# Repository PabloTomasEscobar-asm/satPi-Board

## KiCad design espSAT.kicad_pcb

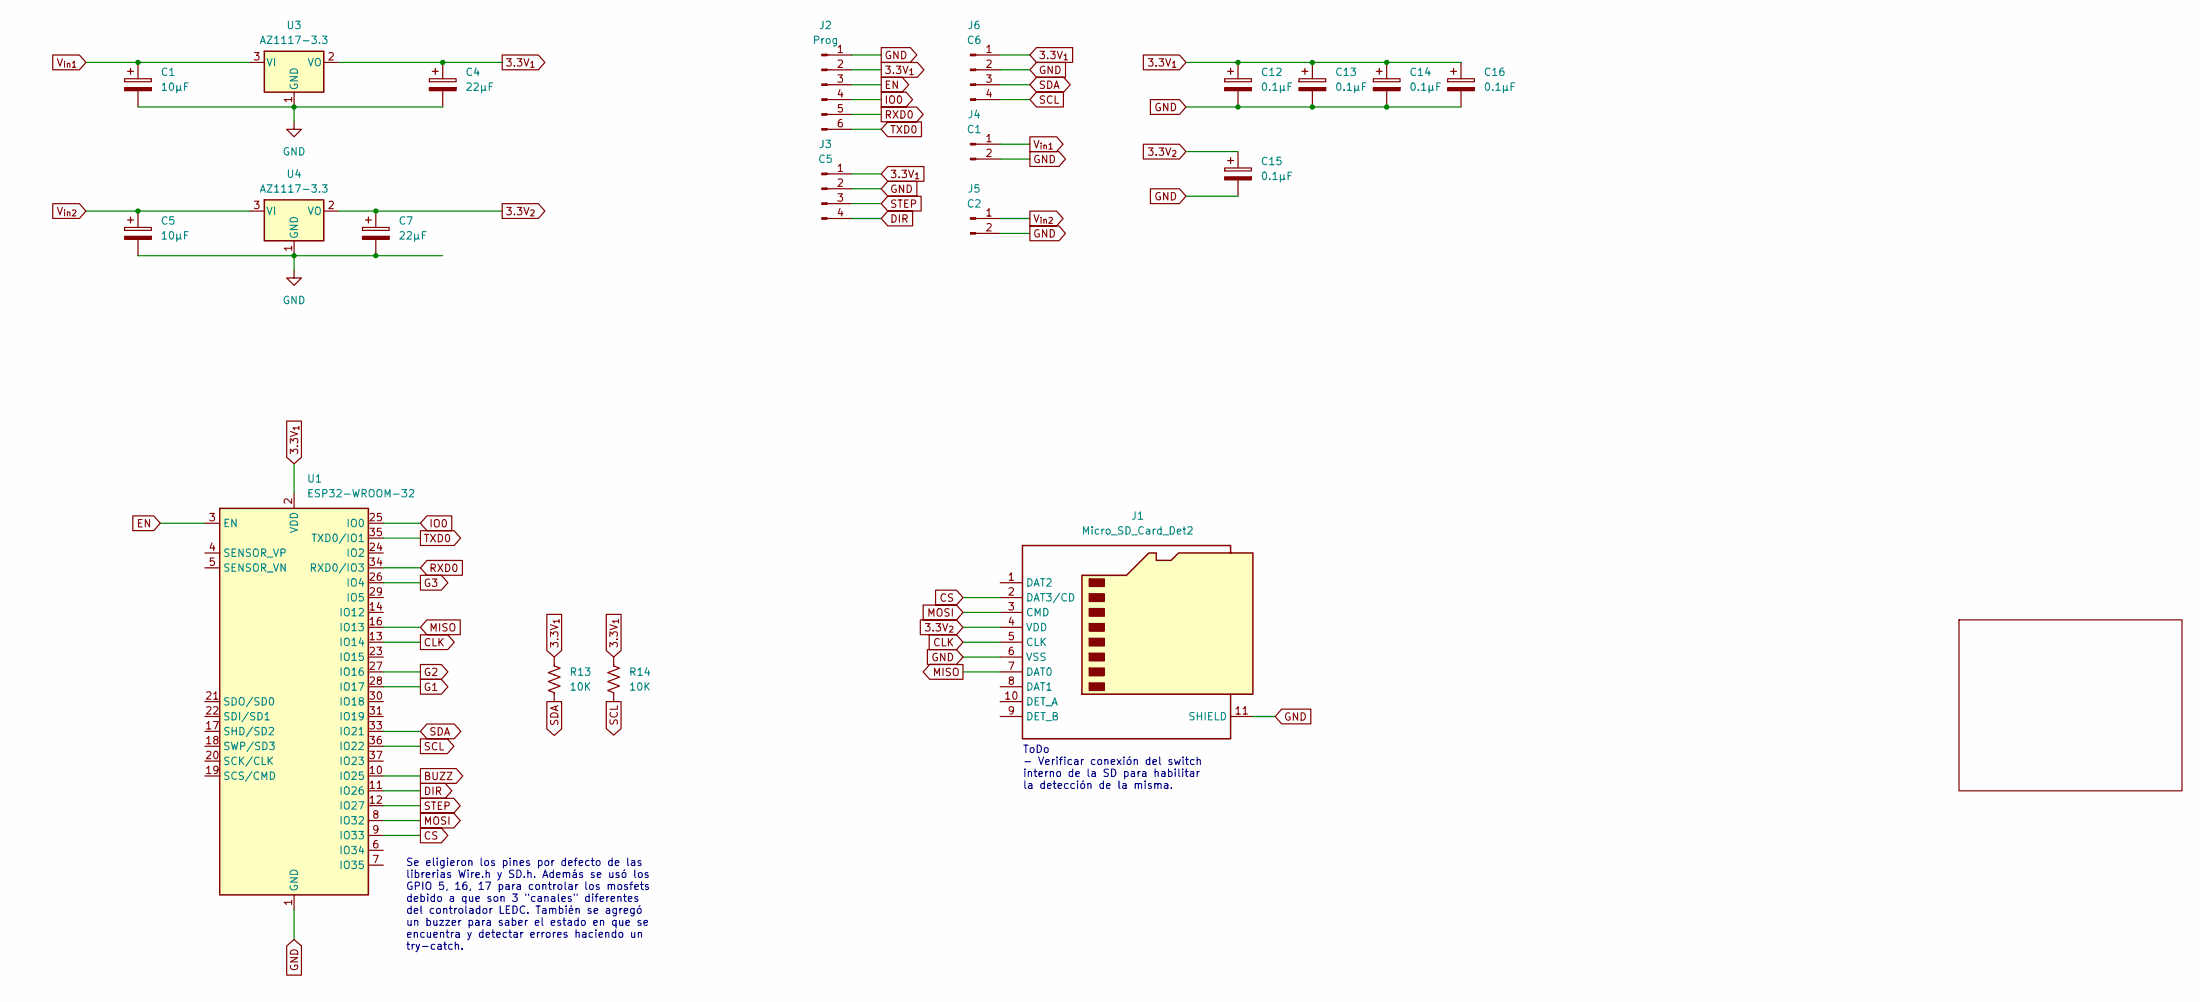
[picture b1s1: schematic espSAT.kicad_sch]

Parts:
C1, C5: 10μF; C_0805_2012Metric_Pad1.18x1.45mm_HandSolder
C4, C7: 22μF; C_0805_2012Metric_Pad1.18x1.45mm_HandSolder
C12, C13, C14, C15, C16: 0.1μF; C_0805_2012Metric_Pad1.18x1.45mm_HandSolder
J1: Micro_SD_Card_Det2; microSD_HC_Hirose_DM3AT-SF-PEJM5
J2: Prog; PinSocket_1x06_P2.54mm_Horizontal
J3: C5; PinSocket_1x04_P1.27mm_Vertical
J4: C1; PinSocket_1x02_P1.27mm_Vertical
J5: C2; PinSocket_1x02_P1.27mm_Vertical
J6: C6; PinSocket_1x04_P1.27mm_Vertical
R13, R14: 10K; R_0805_2012Metric_Pad1.20x1.40mm_HandSolder
U1: ESP32-WROOM-32
U3, U4: AZ1117-3.3; SOT-89-3_Handsoldering

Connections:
3.3V_{1}: C4.1, C12.1, C13.1, C14.1, C16.1, J2.2, J3.1, J6.1, R13.2, R14.2, U1.2 (VDD), U3.2 (VO); also elsewhere on the board
3.3V_{2}: C7.1, C15.1, J1.4 (VDD), U4.2 (VO)
BUZZ: U1.10 (IO25)
CLK: J1.5 (CLK), U1.13 (IO14)
CS: J1.2 (DAT3/CD), U1.9 (IO33)
DIR: J3.4, U1.11 (IO26)
EN: J2.3, U1.3 (EN)
G1: U1.28 (IO17); also elsewhere on the board
G2: U1.27 (IO16); also elsewhere on the board
G3: U1.26 (IO4); also elsewhere on the board
GND: C1.2, C4.2, C5.2, C7.2, C12.2, C13.2, C14.2, C15.2, C16.2, J1.6 (VSS), J1.11 (SHIELD), J2.1, J3.2, J4.2, J5.2, J6.2, U1.1 (GND), U1.15 (GND), U1.38 (GND), U1.39 (GND), U3.1 (GND), U4.1 (GND); also elsewhere on the board
IO0: J2.4, U1.25 (IO0)
MISO: J1.7 (DAT0), U1.16 (IO13)
MOSI: J1.3 (CMD), U1.8 (IO32)
RXD0: J2.5, U1.34 (RXD0/IO3)
SCL: J6.4, R14.1, U1.36 (IO22); also elsewhere on the board
SDA: J6.3, R13.1, U1.33 (IO21); also elsewhere on the board
STEP: J3.3, U1.12 (IO27)
TXD0: J2.6, U1.35 (TXD0/IO1)
V_{in1}: C1.1, J4.1, U3.3 (VI)
V_{in2}: C5.1, J5.1, U4.3 (VI); also elsewhere on the board

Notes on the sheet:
Se eligieron los pines por defecto de las librerias Wire.h y SD.h. Además se usó los GPIO 5, 16, 17 para controlar los mosfets debido a que son 3 "canales" diferentes del controlador LEDC. También se agregó un buzzer para saber el estado en que se encuentra y detectar errores haciendo un try-catch.
ToDo - Verificar conexión del switch interno de la SD para habilitar la detección de la misma.

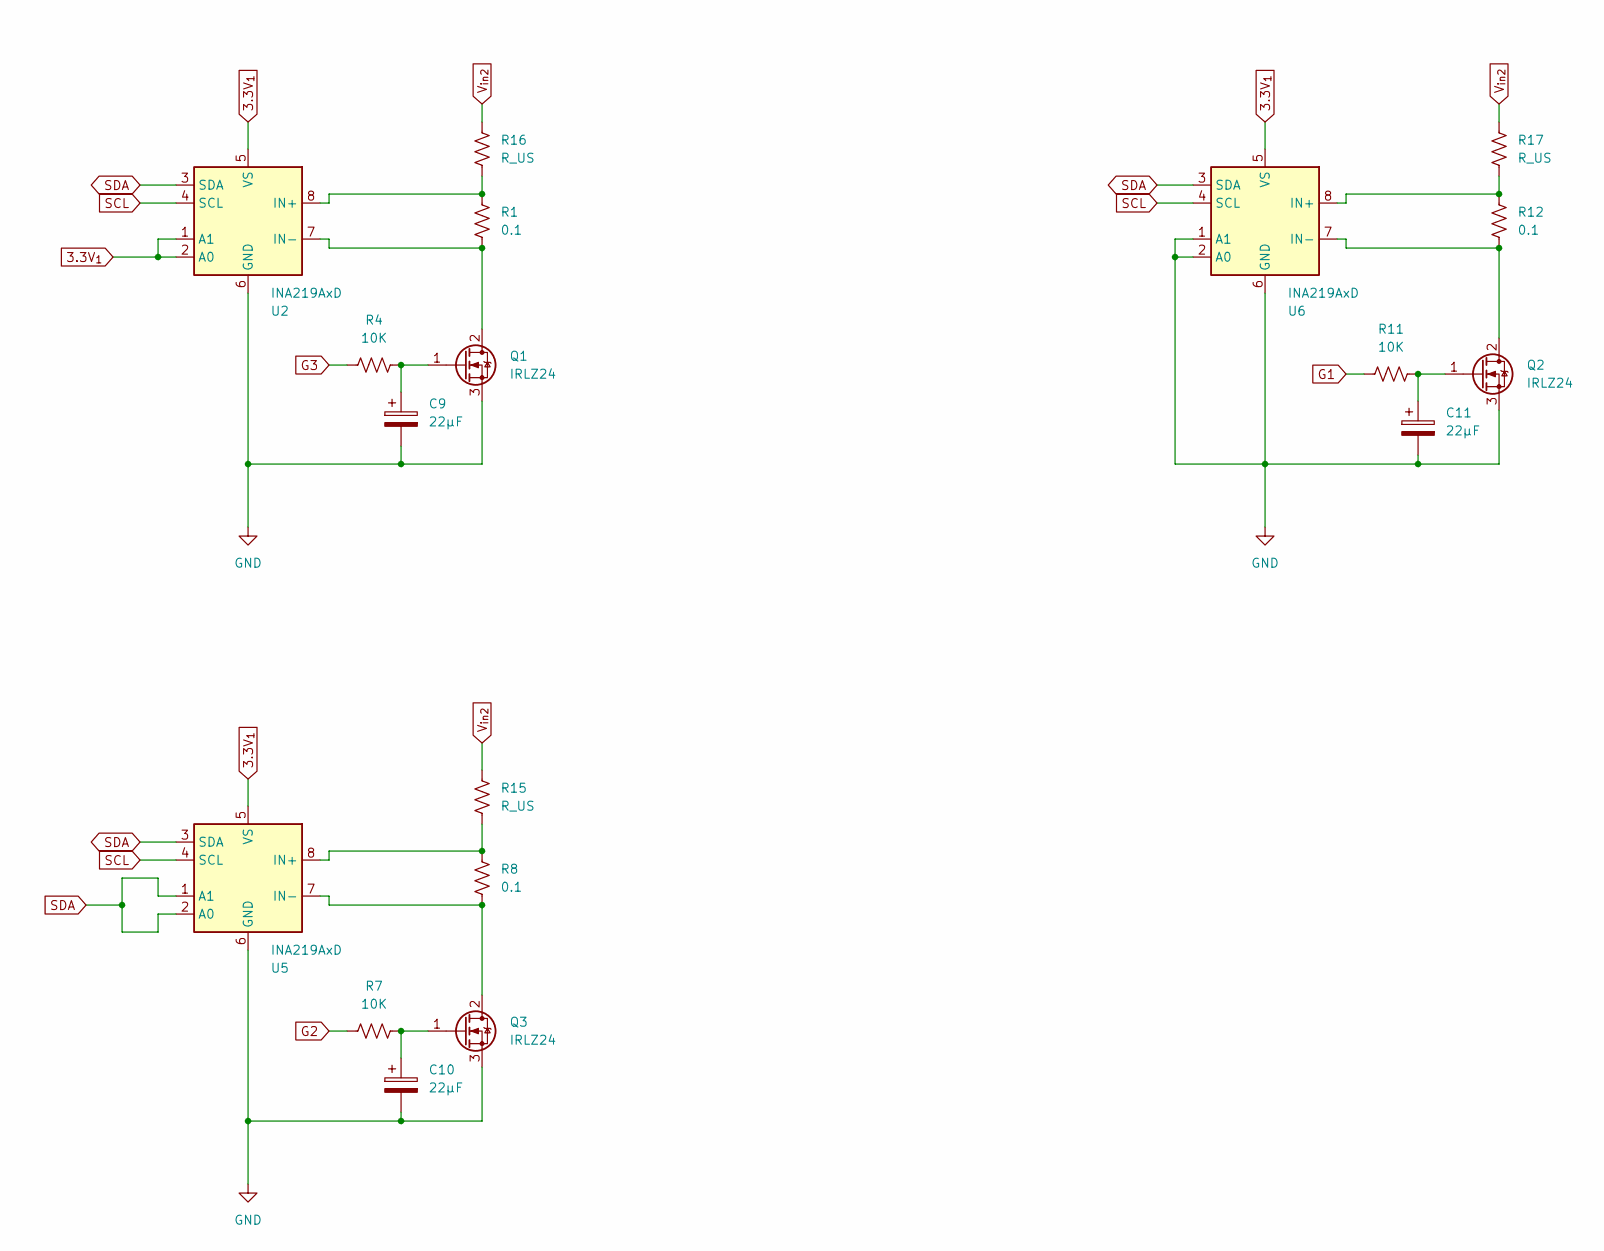
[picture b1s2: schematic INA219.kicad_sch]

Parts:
C9, C10, C11: 22μF; C_0805_2012Metric_Pad1.18x1.45mm_HandSolder
Q1, Q2, Q3: IRLZ24; TO-220-3_Horizontal_TabDown
R1, R8, R12: 0.1; R_2512_6332Metric_Pad1.40x3.35mm_HandSolder
R4, R7, R11: 10K; R_0805_2012Metric_Pad1.20x1.40mm_HandSolder
R15, R16, R17: R_US; R_Axial_DIN0207_L6.3mm_D2.5mm_P15.24mm_Horizontal
U2, U5, U6: INA219AxD; SOIC-8_3.9x4.9mm_P1.27mm

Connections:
3.3V_{1}: U2.1 (A1), U2.2 (A0), U2.5 (VS), U5.5 (VS), U6.5 (VS); also elsewhere on the board
G1: R11.1; also elsewhere on the board
G2: R7.1; also elsewhere on the board
G3: R4.1; also elsewhere on the board
GND: C9.2, C10.2, C11.2, Q1.3 (S), Q2.3 (S), Q3.3 (S), U2.6 (GND), U5.6 (GND), U6.1 (A1), U6.2 (A0), U6.6 (GND); also elsewhere on the board
unnamed: Q1.2 (D), R1.2, U2.7 (IN-)
unnamed: C9.1, Q1.1 (G), R4.2
unnamed: Q2.2 (D), R12.2, U6.7 (IN-)
unnamed: C11.1, Q2.1 (G), R11.2
unnamed: Q3.2 (D), R8.2, U5.7 (IN-)
unnamed: C10.1, Q3.1 (G), R7.2
unnamed: R1.1, R16.2, U2.8 (IN+)
unnamed: R8.1, R15.2, U5.8 (IN+)
unnamed: R12.1, R17.2, U6.8 (IN+)
SCL: U2.4 (SCL), U5.4 (SCL), U6.4 (SCL); also elsewhere on the board
SDA: U2.3 (SDA), U5.1 (A1), U5.2 (A0), U5.3 (SDA), U6.3 (SDA); also elsewhere on the board
V_{in2}: R15.1, R16.1, R17.1; also elsewhere on the board

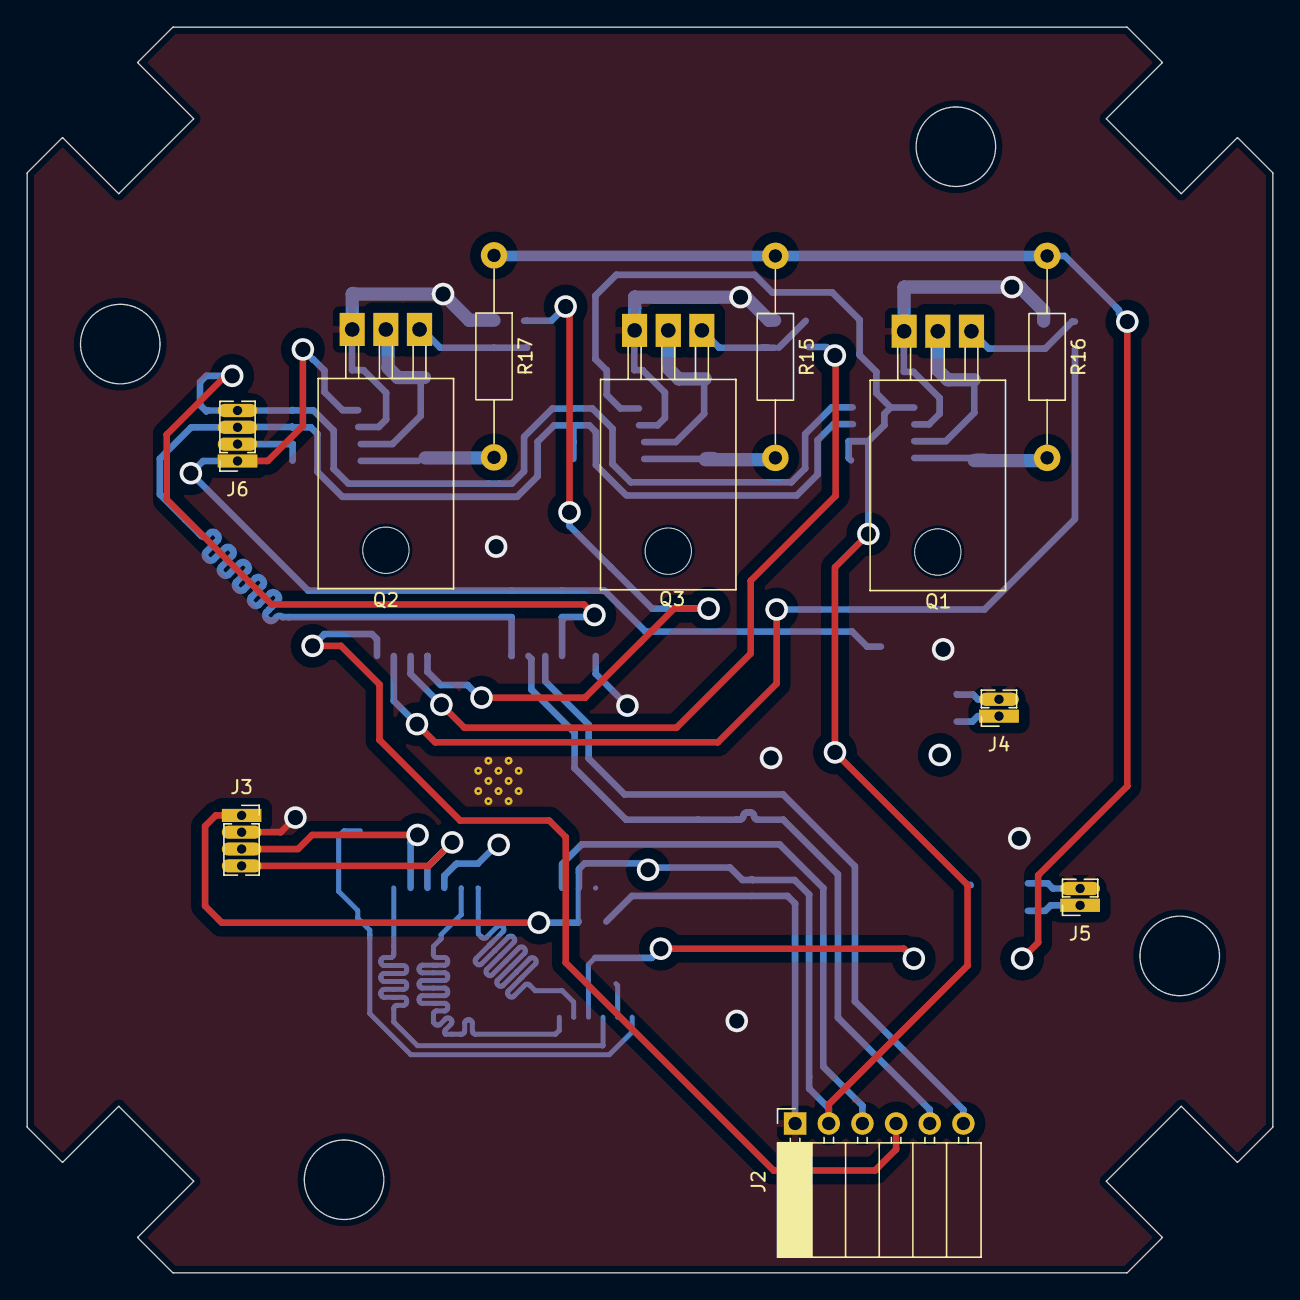
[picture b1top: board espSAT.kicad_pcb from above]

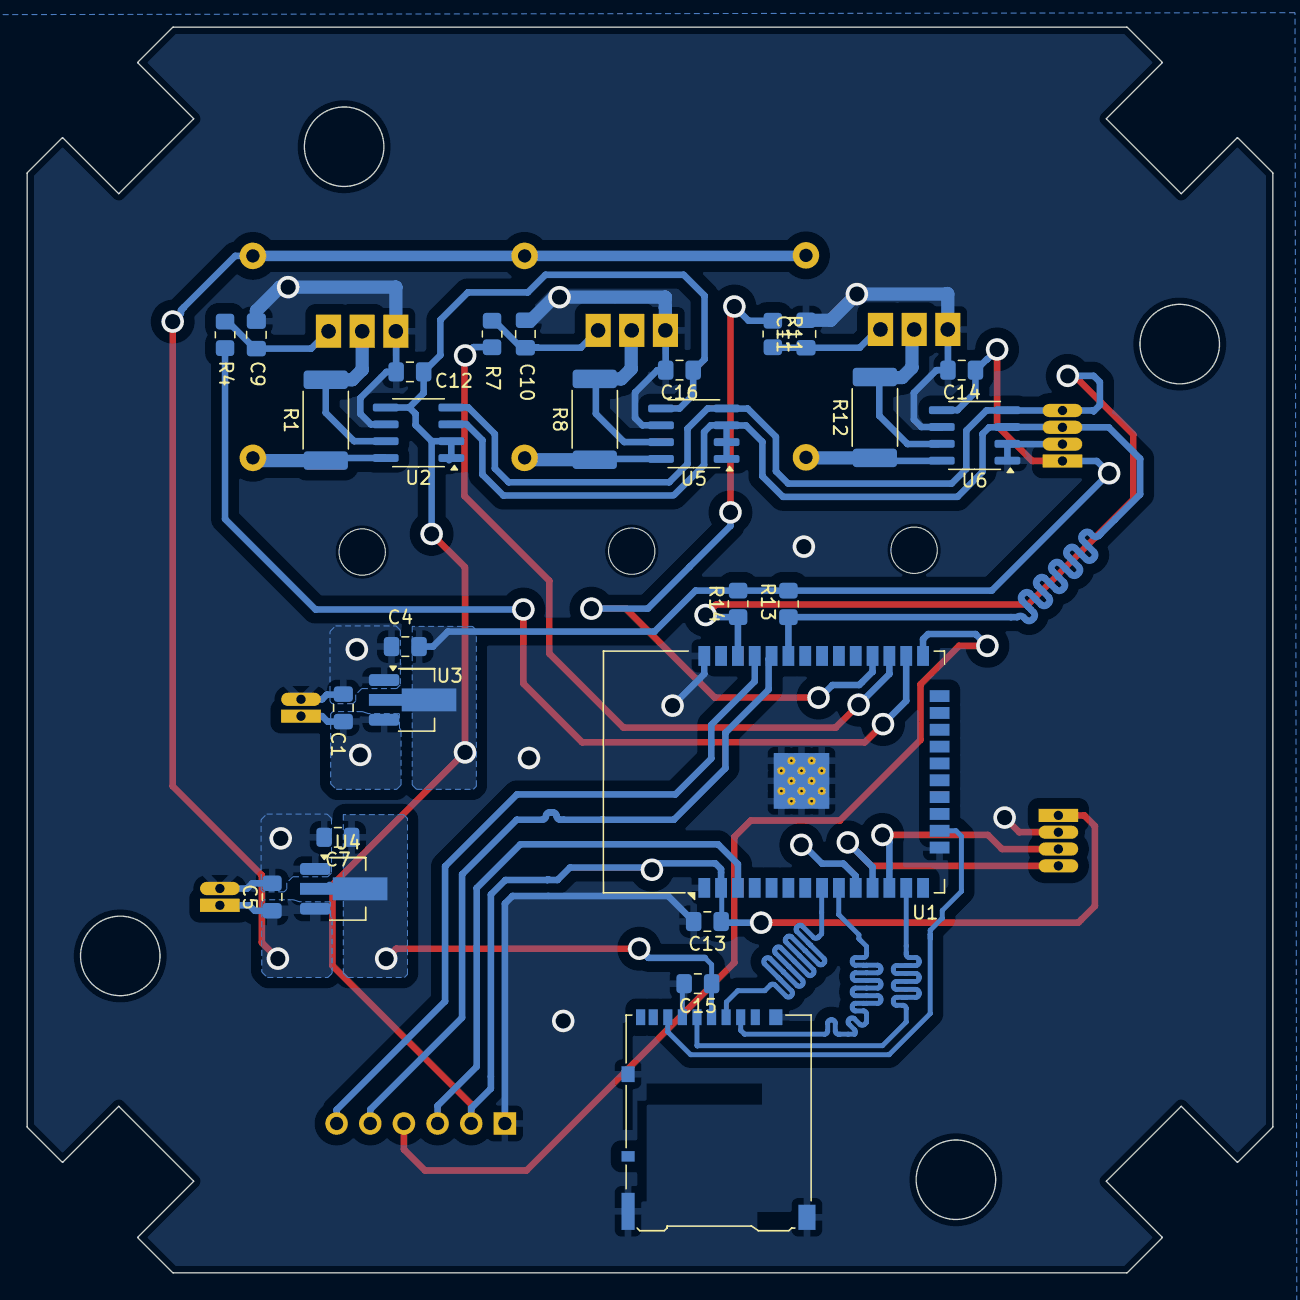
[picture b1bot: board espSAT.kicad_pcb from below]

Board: 2 copper layers, 94.0 x 94.0 mm, 38 parts (27 on the bottom side), 29 nets.

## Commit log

2025-10-30 v1.2
